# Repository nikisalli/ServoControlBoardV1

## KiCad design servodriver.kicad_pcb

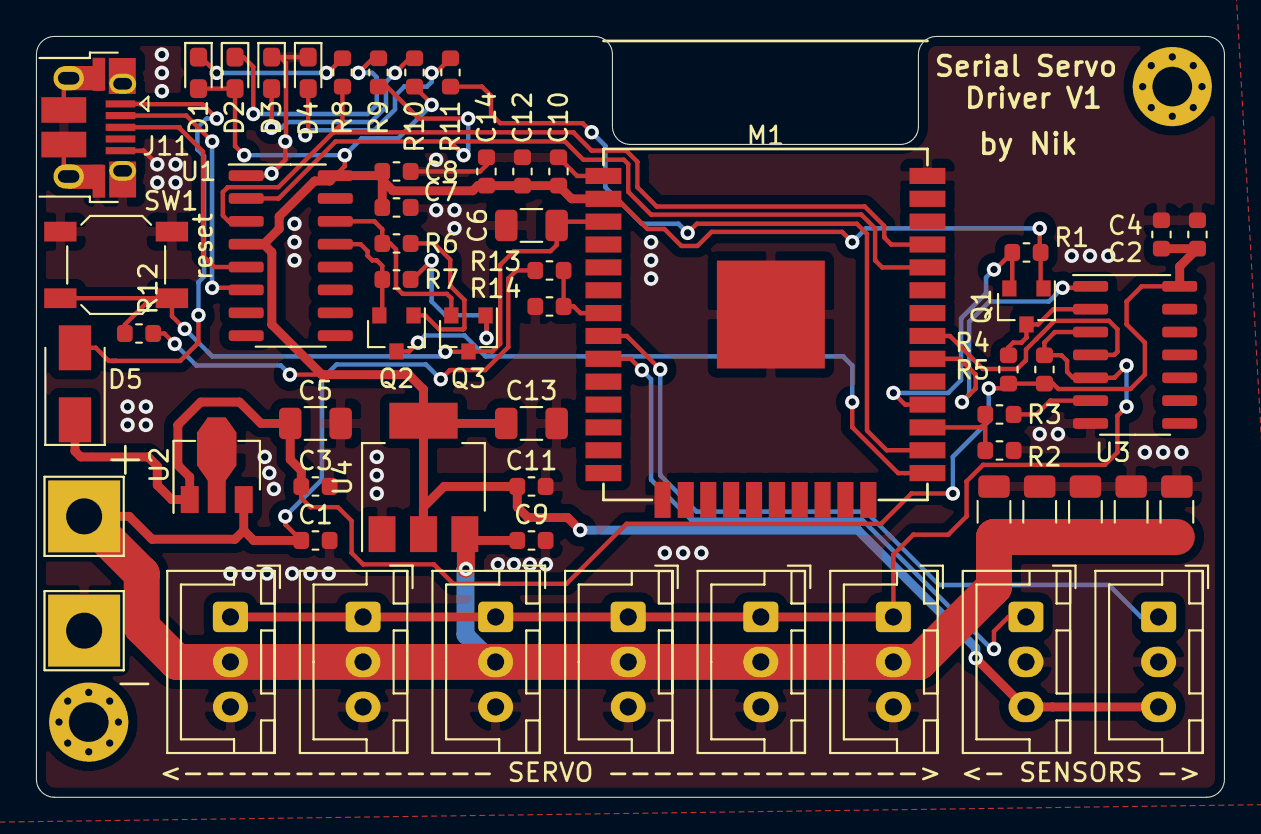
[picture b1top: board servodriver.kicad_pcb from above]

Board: 2 copper layers, 66.0 x 42.3 mm, 60 parts (0 on the bottom side), 30 nets.

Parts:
C1, C2, C3, C7, C9, C10, C11, C12: 100n; C_0603_1608Metric
C4, C8, C14: 1u; C_0603_1608Metric
C5, C6, C13, C15, C16, C17, C18, C19: 10u; C_1206_3216Metric
D1, D2, D3, D4: LED; LED_0603_1608Metric_Pad1.05x0.95mm_HandSolder
D5: 1N5819; D_SMA
J1, J2: Conn_01x01_Male; TestPoint_THTPad_4.0x4.0mm_Drill2.0mm
J3, J4, J5, J6, J7, J8, J9, J10: 01x03; JST_XH_B3B-XH-A_1x03_P2.50mm_Vertical
J11: USB_B_Mini; USB_Micro-B_Amphenol_10103594-0001LF_Horizontal
M1: ESP-32S
MK1, MK2: Mounting_Hole; MountingHole_2.2mm_M2_Pad_Via
Q1, Q2, Q3: 2N7002; SOT-23
R1, R5, R12, R13: 10k; R_0603_1608Metric
R2: 2k; R_0603_1608Metric
R3, R4, R8, R9, R11, R14: 1k; R_0603_1608Metric
R6, R7: 12k; R_0603_1608Metric
R10: 1.5k; R_0603_1608Metric
SW1: SW_Push; SW_SPST_SKQG_WithoutStem
U1: CH340G; SOIC-16_3.9x9.9mm_P1.27mm
U2: L78L05_SOT89; SOT-89-3
U3: 74LS125; SOIC-14_3.9x8.7mm_P1.27mm
U4: AMS1117-3.3; SOT-223-3_TabPin2

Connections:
+3V3: C7.1, C8.1, C10.1, C11.1, C12.1, C13.1, C14.1, D1.2, D2.2, J4.3, J10.3, M1.2, Q1.1, R1.1, R10.1, R12.1, U1.4, U1.16, U4.2
+5V: C2.1, C3.1, C4.1, C5.1, D5.1, R4.1, R5.1, U2.1, U3.14
BAT_M: M1.7, R13.2, R14.1
D+: J11.3, U1.5
D-: J11.2, U1.6
EN: C6.1, M1.3, Q3.3, R12.2, SW1.2
GND: C1.2, C2.2, C3.2, C4.2, C5.2, C6.2, C7.2, C8.2, C9.2, C10.2, C11.2, C12.2, C13.2, C14.2, C15.2, C16.2, C17.2, C18.2, C19.2, D3.1, D4.1, J2.1, J3.3, J4.2, J5.3, J6.3, J7.3, J8.3, J9.3, J10.2, J11.5, J11.6, M1.1, M1.15, M1.38, R2.2, R14.2, SW1.1, U1.1, U2.2, U3.7, U4.1
IO0: M1.25, Q2.3
IO4: M1.26, R11.1
unnamed: D1.1, R8.2
unnamed: D2.1, R9.2
unnamed: D3.2, R10.2
unnamed: D4.2, R11.2
unnamed: D5.2, J11.1
unnamed: Q1.3, R4.2, U3.2
unnamed: Q2.1, R6.1
unnamed: Q2.2, R7.2, U1.13
unnamed: Q3.1, R7.1
unnamed: Q3.2, R6.2, U1.14
unnamed: R3.1, U3.6
SENS_1: J4.1, M1.8
SENS_2: J10.1, M1.9
S_RX: M1.27, R2.1, R3.2
S_RX_ENB: M1.31, U3.4
S_SERIAL: J3.1, J5.1, J6.1, J7.1, J8.1, J9.1, R5.2, U3.3, U3.5
S_TX: M1.28, Q1.2, R1.2
S_TX_ENB: M1.30, U3.1
USB_RX: M1.35, R8.1, U1.3
USB_TX: M1.34, R9.1, U1.2
VBUS: C1.1, C9.1, C15.1, C16.1, C17.1, C18.1, C19.1, J1.1, J3.2, J5.2, J6.2, J7.2, J8.2, J9.2, R13.1, U2.3, U4.3
